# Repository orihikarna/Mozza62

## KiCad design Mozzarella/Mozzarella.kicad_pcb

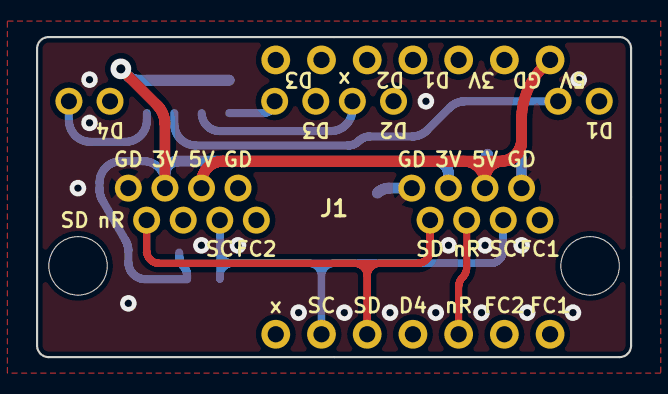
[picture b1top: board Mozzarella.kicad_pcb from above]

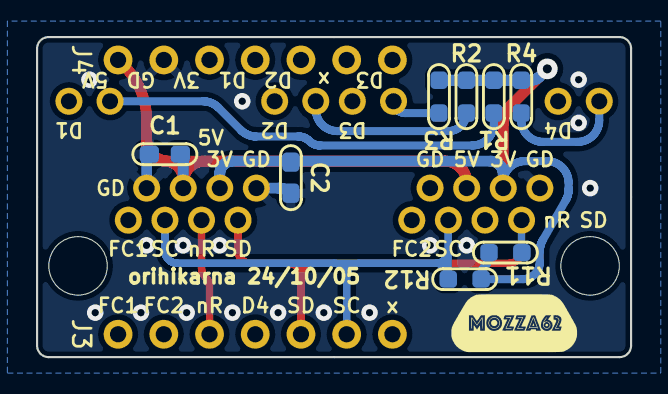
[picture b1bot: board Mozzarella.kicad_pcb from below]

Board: 4 copper layers, 33.0 x 17.8 mm, 12 parts (11 on the bottom side), 16 nets.

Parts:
C1, C2: 0.1u; C_1608_HandSolder
G1: LOGO; mozza62_logo2
J1: RJ45_LED_Shielded_x2; RJ45_Amphenol_RJHSE508X-02
J3, J4: Conn_01x07; PinHeader_1x07_P2.54mm_Vertical
R1, R2, R3, R4: 1k; R_1608_HandSolder
R11, R12: 2.2k; R_1608_HandSolder

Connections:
3V3: C2.1, J1.6, J1.18, J4.3, R1.1, R2.1, R3.1, R4.1, R11.2, R12.2
5VD: C1.1, J1.4, J1.16, J4.1
GND: C1.2, C2.2, J1.2, J1.8, J1.14, J1.20, J4.2
LED1: J1.9, J4.4
LED2: J1.11, J4.5
LED3: J1.21, J4.7
LED4: J1.23, J3.4
NRST: J1.5, J1.17, J3.3
unnamed: J1.10, R1.2
unnamed: J1.12, R2.2
unnamed: J1.22, R3.2
unnamed: J1.24, R4.2
RGB1: J1.1, J3.1
RGB2: J1.13, J3.2
SCK: J1.3, J1.15, J3.6, R12.1
SDA: J1.7, J1.19, J3.5, R11.1

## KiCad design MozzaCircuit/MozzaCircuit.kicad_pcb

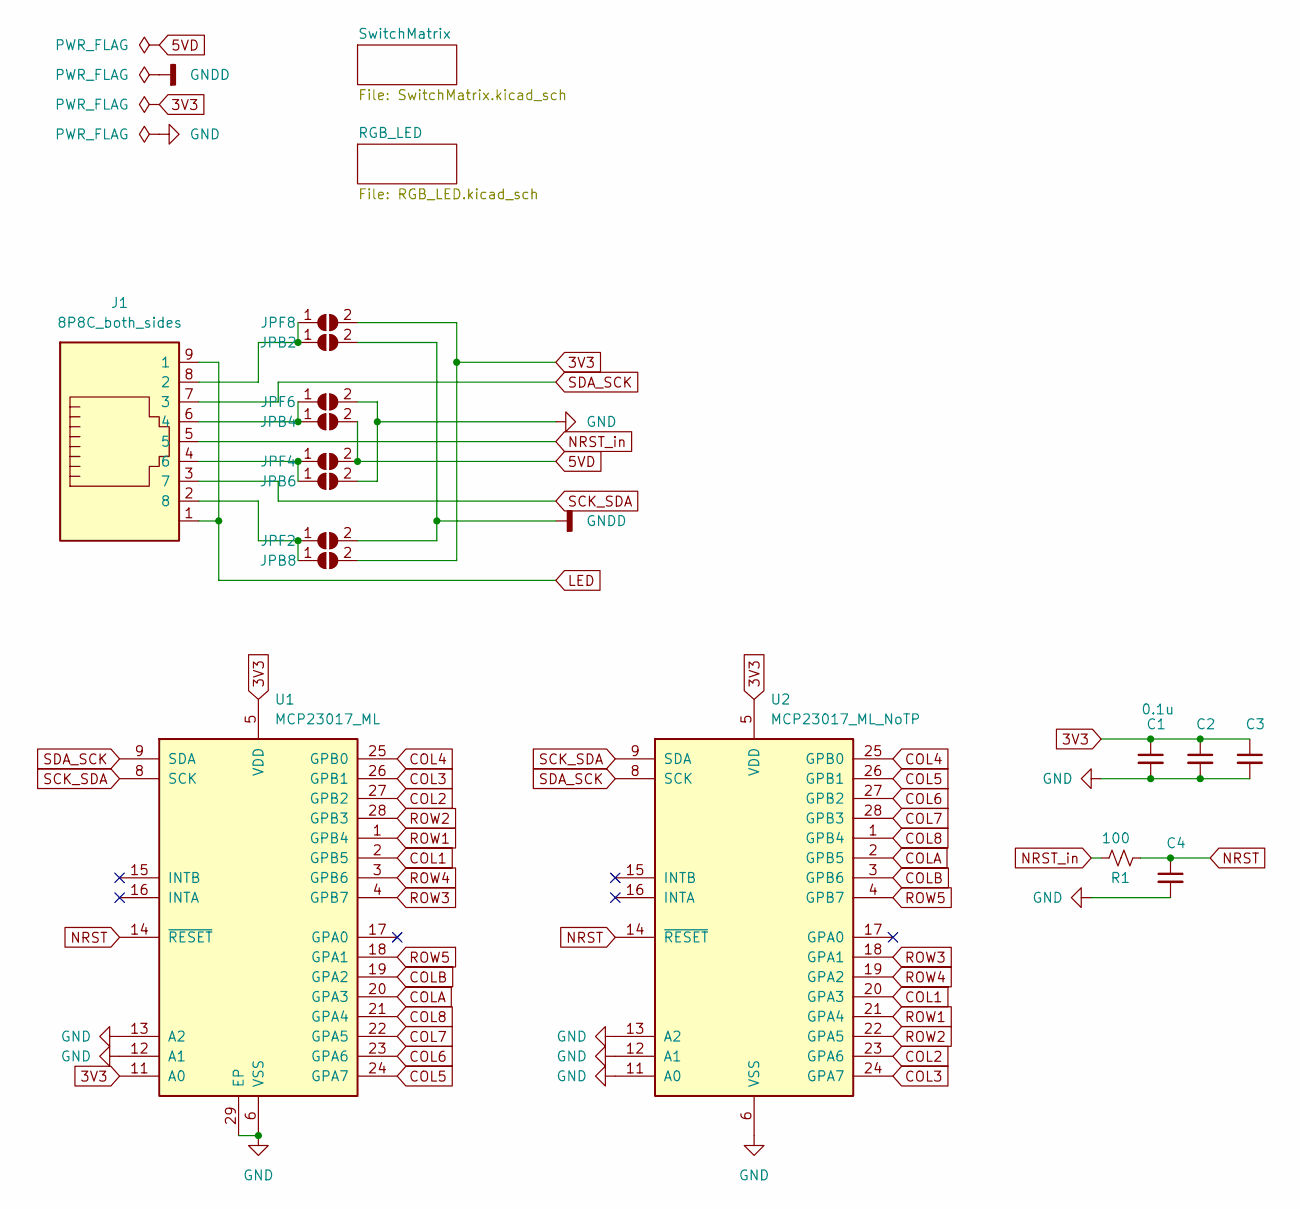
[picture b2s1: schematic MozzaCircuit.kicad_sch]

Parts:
C1: 0.1u; C_1608_HandSolder
C2: C_Small; C_1608_HandSolder
C3, C4: C_Small; C_1608_HandSolder_both_sides
J1: 8P8C_both_sides; RJ45_Molex_0955032884_both_sides
JPB2, JPB4, JPB6, JPB8: SolderJumper_2_Open; SolderJumper-2_P1.3mm_Open_TrianglePad1.0x1.5mm
JPF2, JPF4, JPF6, JPF8: SolderJumper_2_Open; SolderJumper-2_P1.3mm_Open_TrianglePad1.0x1.5mm
R1: 100; R_1608_HandSolder_both_sides
U1: MCP23017_ML; QFN-28-1EP_6x6mm_P0.65mm_EP4.25x4.25mm_Hand
U2: MCP23017_ML_NoTP; QFN-28-1EP_6x6mm_P0.65mm_EP4.25x4.25mm_Hand_NoTP

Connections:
3V3: C1.1, C2.1, C3.1, JPB8.2 (B), JPF8.2 (B), U1.5 (VDD), U1.11 (A0), U2.5 (VDD); also elsewhere on the board
5VD: JPB4.2 (B), JPF4.2 (B); also elsewhere on the board
COL1: U1.2 (GPB5), U2.20 (GPA3); also elsewhere on the board
COL2: U1.27 (GPB2), U2.23 (GPA6); also elsewhere on the board
COL3: U1.26 (GPB1), U2.24 (GPA7); also elsewhere on the board
COL4: U1.25 (GPB0), U2.25 (GPB0); also elsewhere on the board
COL5: U1.24 (GPA7), U2.26 (GPB1); also elsewhere on the board
COL6: U1.23 (GPA6), U2.27 (GPB2); also elsewhere on the board
COL7: U1.22 (GPA5), U2.28 (GPB3); also elsewhere on the board
COL8: U1.21 (GPA4), U2.1 (GPB4); also elsewhere on the board
COLA: U1.20 (GPA3), U2.2 (GPB5); also elsewhere on the board
COLB: U1.19 (GPA2), U2.3 (GPB6); also elsewhere on the board
GND: C1.2, C2.2, C3.2, C4.2, JPB6.2 (B), JPF6.2 (B), U1.6 (VSS), U1.12 (A1), U1.13 (A2), U1.29 (EP), U2.6 (VSS), U2.11 (A0), U2.12 (A1), U2.13 (A2); also elsewhere on the board
GNDD: JPB2.2 (B), JPF2.2 (B); also elsewhere on the board
LED: J1.1, J1.9 (1); also elsewhere on the board
NRST: C4.1, R1.2, U1.14 (~RESET), U2.14 (~RESET)
NRST_in: J1.5, R1.1
unnamed: J1.2 (8), JPB8.1 (A), JPF2.1 (A)
unnamed: J1.4 (6), JPB6.1 (A), JPF4.1 (A)
unnamed: J1.6 (4), JPB4.1 (A), JPF6.1 (A)
unnamed: J1.8 (2), JPB2.1 (A), JPF8.1 (A)
ROW1: U1.1 (GPB4), U2.21 (GPA4); also elsewhere on the board
ROW2: U1.28 (GPB3), U2.22 (GPA5); also elsewhere on the board
ROW3: U1.4 (GPB7), U2.18 (GPA1); also elsewhere on the board
ROW4: U1.3 (GPB6), U2.19 (GPA2); also elsewhere on the board
ROW5: U1.18 (GPA1), U2.4 (GPB7); also elsewhere on the board
SCK_SDA: J1.3 (7), U1.8 (SCK), U2.9 (SDA)
SDA_SCK: J1.7 (3), U1.9 (SDA), U2.8 (SCK)

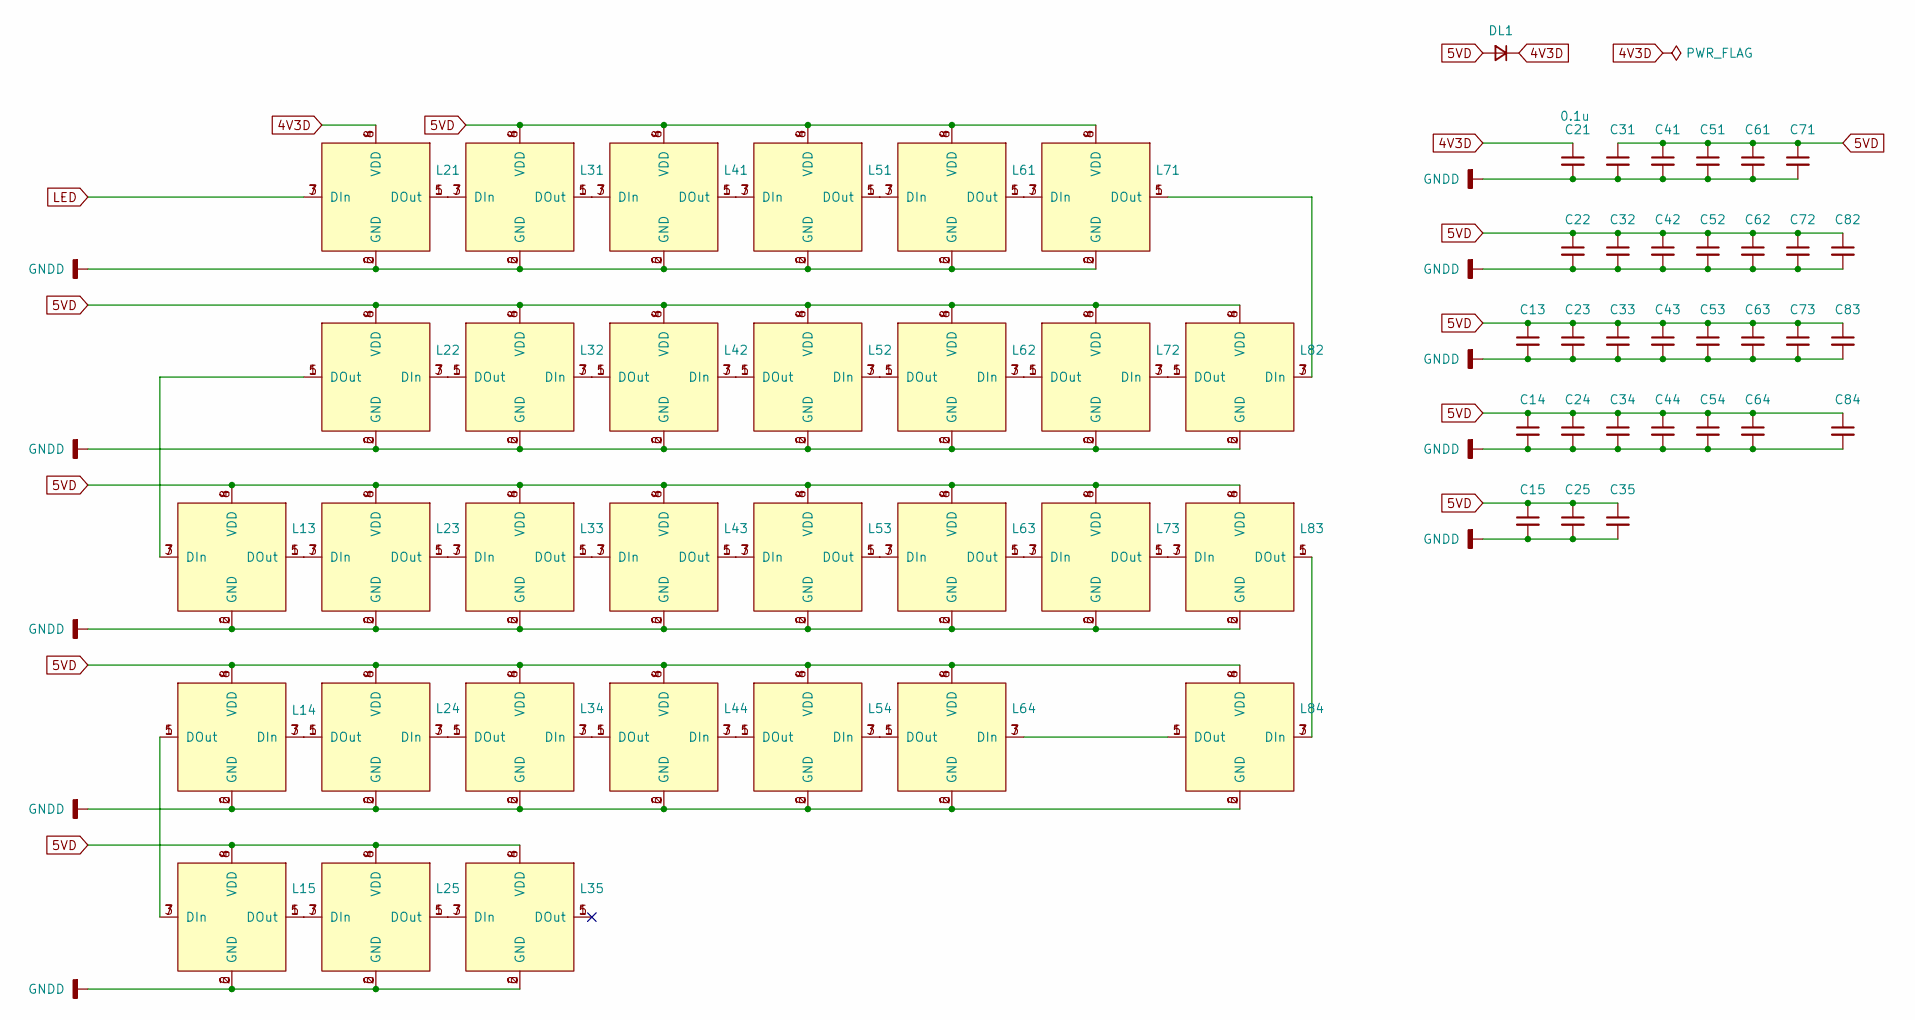
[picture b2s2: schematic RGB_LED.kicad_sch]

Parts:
C13, C14, C15, C22, C23, C24, C25, C31, C32, C33, C34, C35, C41, C42, C43, C44, C51, C52, C53, C54, C61, C62, C63, C64, C71, C72, C73, C82, C83, C84: C_Small; C_1608_HandSolder_both_sides
C21: 0.1u; C_1608_HandSolder_both_sides
DL1: D_Small; D_SOD-323_both_sides
L13, L14, L15, L21, L22, L23, L24, L25, L31, L32, L33, L34, L35, L41, L42, L43, L44, L51, L52, L53, L54, L61, L62, L63, L64, L71, L72, L73, L82, L83, L84: WS2812-2020_both_sides; WS2812B_2020_rev

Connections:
4V3D: C21.1, DL1.1 (K), L21.4 (VDD), L21.8; also elsewhere on the board
5VD: C13.1, C14.1, C15.1, C22.1, C23.1, C24.1, C25.1, C31.1, C32.1, C33.1, C34.1, C35.1, C41.1, C42.1, C43.1, C44.1, C51.1, C52.1, C53.1, C54.1, C61.1, C62.1, C63.1, C64.1, C71.1, C72.1, C73.1, C82.1, C83.1, C84.1, DL1.2 (A), L13.4 (VDD), L13.8, L14.4 (VDD), L14.8, L15.4 (VDD), L15.8, L22.4 (VDD), L22.8, L23.4 (VDD), L23.8, L24.4 (VDD), L24.8, L25.4 (VDD), L25.8, L31.4 (VDD), L31.8, L32.4 (VDD), L32.8, L33.4 (VDD), L33.8, L34.4 (VDD), L34.8, L35.4 (VDD), L35.8, L41.4 (VDD), L41.8, L42.4 (VDD), L42.8, L43.4 (VDD), L43.8, L44.4 (VDD), L44.8, L51.4 (VDD), L51.8, L52.4 (VDD), L52.8, L53.4 (VDD), L53.8, L54.4 (VDD), L54.8, L61.4 (VDD), L61.8, L62.4 (VDD), L62.8, L63.4 (VDD), L63.8, L64.4 (VDD), L64.8, L71.4 (VDD), L71.8, L72.4 (VDD), L72.8, L73.4 (VDD), L73.8, L82.4 (VDD), L82.8, L83.4 (VDD), L83.8, L84.4 (VDD), L84.8; also elsewhere on the board
GNDD: C13.2, C14.2, C15.2, C21.2, C22.2, C23.2, C24.2, C25.2, C31.2, C32.2, C33.2, C34.2, C35.2, C41.2, C42.2, C43.2, C44.2, C51.2, C52.2, C53.2, C54.2, C61.2, C62.2, C63.2, C64.2, C71.2, C72.2, C73.2, C82.2, C83.2, C84.2, L13.2 (GND), L13.6, L14.2 (GND), L14.6, L15.2 (GND), L15.6, L21.2 (GND), L21.6, L22.2 (GND), L22.6, L23.2 (GND), L23.6, L24.2 (GND), L24.6, L25.2 (GND), L25.6, L31.2 (GND), L31.6, L32.2 (GND), L32.6, L33.2 (GND), L33.6, L34.2 (GND), L34.6, L35.2 (GND), L35.6, L41.2 (GND), L41.6, L42.2 (GND), L42.6, L43.2 (GND), L43.6, L44.2 (GND), L44.6, L51.2 (GND), L51.6, L52.2 (GND), L52.6, L53.2 (GND), L53.6, L54.2 (GND), L54.6, L61.2 (GND), L61.6, L62.2 (GND), L62.6, L63.2 (GND), L63.6, L64.2 (GND), L64.6, L71.2 (GND), L71.6, L72.2 (GND), L72.6, L73.2 (GND), L73.6, L82.2 (GND), L82.6, L83.2 (GND), L83.6, L84.2 (GND), L84.6; also elsewhere on the board
LED: L21.3 (DIn), L21.7 (DIn); also elsewhere on the board
unnamed: L13.1 (DOut), L13.5 (DOut), L23.3 (DIn), L23.7 (DIn)
unnamed: L13.3 (DIn), L13.7 (DIn), L22.1 (DOut), L22.5 (DOut)
unnamed: L14.1 (DOut), L14.5 (DOut), L15.3 (DIn), L15.7 (DIn)
unnamed: L14.3 (DIn), L14.7 (DIn), L24.1 (DOut), L24.5 (DOut)
unnamed: L15.1 (DOut), L15.5 (DOut), L25.3 (DIn), L25.7 (DIn)
unnamed: L21.1 (DOut), L21.5 (DOut), L31.3 (DIn), L31.7 (DIn)
unnamed: L22.3 (DIn), L22.7 (DIn), L32.1 (DOut), L32.5 (DOut)
unnamed: L23.1 (DOut), L23.5 (DOut), L33.3 (DIn), L33.7 (DIn)
unnamed: L24.3 (DIn), L24.7 (DIn), L34.1 (DOut), L34.5 (DOut)
unnamed: L25.1 (DOut), L25.5 (DOut), L35.3 (DIn), L35.7 (DIn)
unnamed: L31.1 (DOut), L31.5 (DOut), L41.3 (DIn), L41.7 (DIn)
unnamed: L32.3 (DIn), L32.7 (DIn), L42.1 (DOut), L42.5 (DOut)
unnamed: L33.1 (DOut), L33.5 (DOut), L43.3 (DIn), L43.7 (DIn)
unnamed: L34.3 (DIn), L34.7 (DIn), L44.1 (DOut), L44.5 (DOut)
unnamed: L41.1 (DOut), L41.5 (DOut), L51.3 (DIn), L51.7 (DIn)
unnamed: L42.3 (DIn), L42.7 (DIn), L52.1 (DOut), L52.5 (DOut)
unnamed: L43.1 (DOut), L43.5 (DOut), L53.3 (DIn), L53.7 (DIn)
unnamed: L44.3 (DIn), L44.7 (DIn), L54.1 (DOut), L54.5 (DOut)
unnamed: L51.1 (DOut), L51.5 (DOut), L61.3 (DIn), L61.7 (DIn)
unnamed: L52.3 (DIn), L52.7 (DIn), L62.1 (DOut), L62.5 (DOut)
unnamed: L53.1 (DOut), L53.5 (DOut), L63.3 (DIn), L63.7 (DIn)
unnamed: L54.3 (DIn), L54.7 (DIn), L64.1 (DOut), L64.5 (DOut)
unnamed: L61.1 (DOut), L61.5 (DOut), L71.3 (DIn), L71.7 (DIn)
unnamed: L62.3 (DIn), L62.7 (DIn), L72.1 (DOut), L72.5 (DOut)
unnamed: L63.1 (DOut), L63.5 (DOut), L73.3 (DIn), L73.7 (DIn)
unnamed: L64.3 (DIn), L64.7 (DIn), L84.1 (DOut), L84.5 (DOut)
unnamed: L71.1 (DOut), L71.5 (DOut), L82.3 (DIn), L82.7 (DIn)
unnamed: L72.3 (DIn), L72.7 (DIn), L82.1 (DOut), L82.5 (DOut)
unnamed: L73.1 (DOut), L73.5 (DOut), L83.3 (DIn), L83.7 (DIn)
unnamed: L83.1 (DOut), L83.5 (DOut), L84.3 (DIn), L84.7 (DIn)

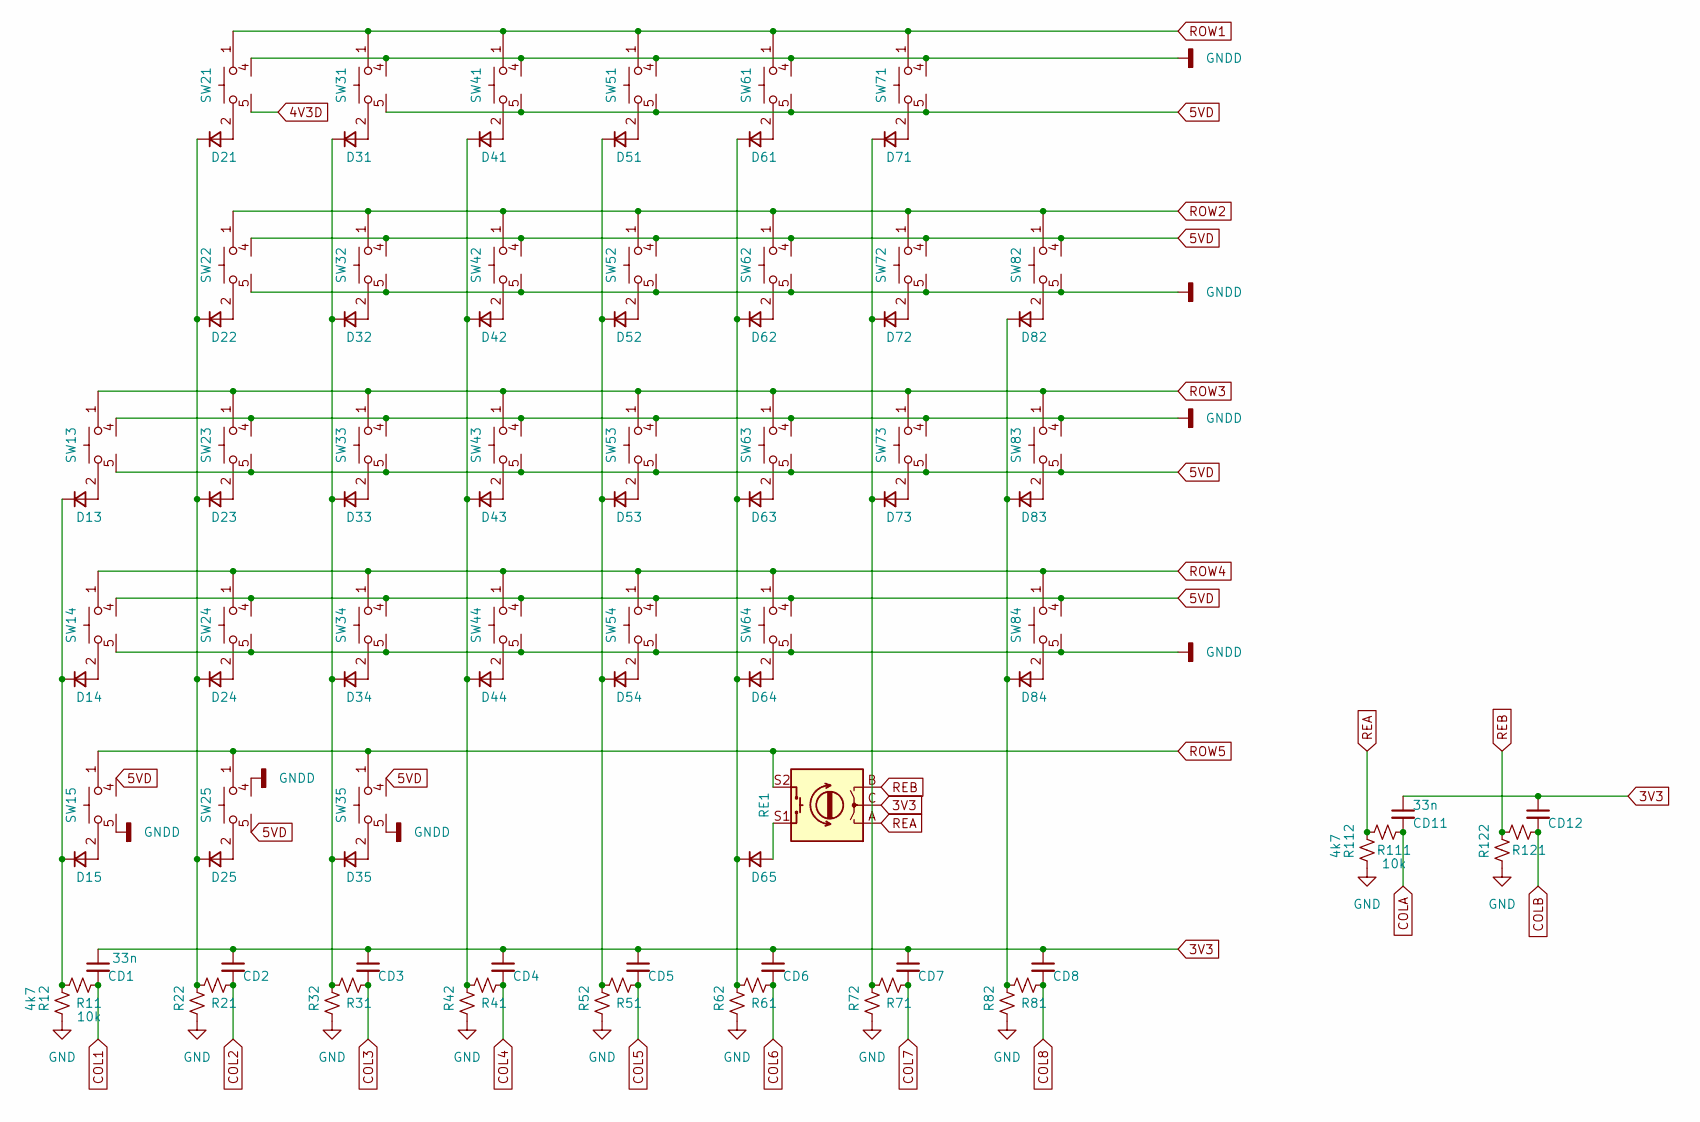
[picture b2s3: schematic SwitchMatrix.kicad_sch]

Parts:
CD1, CD11: 33n; C_1608_HandSolder_both_sides
CD2, CD3, CD4, CD5, CD6, CD7, CD8, CD12: C_Small; C_1608_HandSolder_both_sides
D13, D14, D15, D21, D22, D23, D24, D25, D31, D32, D33, D34, D35, D41, D42, D43, D44, D51, D52, D53, D54, D61, D62, D63, D64, D65, D71, D72, D73, D82, D83, D84: D_Small; D_SOD-323_both_sides
R11, R111: 10k; R_1608_HandSolder_both_sides
R12, R112: 4k7; R_1608_HandSolder_both_sides
R21, R22, R31, R32, R41, R42, R51, R52, R61, R62, R71, R72, R81, R82, R121, R122: R_Small_US; R_1608_HandSolder_both_sides
RE1: RotaryEncoder_Switch; RotaryEncoder_Bourns_PEC12R-4215F
SW13, SW14, SW15, SW21, SW22, SW23, SW24, SW25, SW31, SW32, SW33, SW34, SW35, SW41, SW42, SW43, SW44, SW51, SW52, SW53, SW54, SW61, SW62, SW63, SW64, SW71, SW72, SW73, SW82, SW83, SW84: SW_ChocV2_rev; ChocV2_rev

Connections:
3V3: CD1.1, CD2.1, CD3.1, CD4.1, CD5.1, CD6.1, CD7.1, CD8.1, CD11.1, CD12.1, RE1.C; also elsewhere on the board
4V3D: SW21.5; also elsewhere on the board
5VD: SW13.5, SW14.4, SW15.4, SW22.4, SW23.5, SW24.4, SW25.5, SW31.5, SW32.4, SW33.5, SW34.4, SW35.4, SW41.5, SW42.4, SW43.5, SW44.4, SW51.5, SW52.4, SW53.5, SW54.4, SW61.5, SW62.4, SW63.5, SW64.4, SW71.5, SW72.4, SW73.5, SW82.4, SW83.5, SW84.4; also elsewhere on the board
COL1: CD1.2, R11.2; also elsewhere on the board
COL2: CD2.2, R21.2; also elsewhere on the board
COL3: CD3.2, R31.2; also elsewhere on the board
COL4: CD4.2, R41.2; also elsewhere on the board
COL5: CD5.2, R51.2; also elsewhere on the board
COL6: CD6.2, R61.2; also elsewhere on the board
COL7: CD7.2, R71.2; also elsewhere on the board
COL8: CD8.2, R81.2; also elsewhere on the board
COLA: CD11.2, R111.2; also elsewhere on the board
COLB: CD12.2, R121.2; also elsewhere on the board
GND: R12.2, R22.2, R32.2, R42.2, R52.2, R62.2, R72.2, R82.2, R112.2, R122.2; also elsewhere on the board
GNDD: SW13.4, SW14.5, SW15.5, SW21.4, SW22.5, SW23.4, SW24.5, SW25.4, SW31.4, SW32.5, SW33.4, SW34.5, SW35.5, SW41.4, SW42.5, SW43.4, SW44.5, SW51.4, SW52.5, SW53.4, SW54.5, SW61.4, SW62.5, SW63.4, SW64.5, SW71.4, SW72.5, SW73.4, SW82.5, SW83.4, SW84.5; also elsewhere on the board
unnamed: D13.1 (K), D14.1 (K), D15.1 (K), R11.1, R12.1
unnamed: D13.2 (A), SW13.2, SW13.3
unnamed: D14.2 (A), SW14.2, SW14.3
unnamed: D15.2 (A), SW15.2, SW15.3
unnamed: D21.1 (K), D22.1 (K), D23.1 (K), D24.1 (K), D25.1 (K), R21.1, R22.1
unnamed: D21.2 (A), SW21.2, SW21.3
unnamed: D22.2 (A), SW22.2, SW22.3
unnamed: D23.2 (A), SW23.2, SW23.3
unnamed: D24.2 (A), SW24.2, SW24.3
unnamed: D25.2 (A), SW25.2, SW25.3
unnamed: D31.1 (K), D32.1 (K), D33.1 (K), D34.1 (K), D35.1 (K), R31.1, R32.1
unnamed: D31.2 (A), SW31.2, SW31.3
unnamed: D32.2 (A), SW32.2, SW32.3
unnamed: D33.2 (A), SW33.2, SW33.3
unnamed: D34.2 (A), SW34.2, SW34.3
unnamed: D35.2 (A), SW35.2, SW35.3
unnamed: D41.1 (K), D42.1 (K), D43.1 (K), D44.1 (K), R41.1, R42.1
unnamed: D41.2 (A), SW41.2, SW41.3
unnamed: D42.2 (A), SW42.2, SW42.3
unnamed: D43.2 (A), SW43.2, SW43.3
unnamed: D44.2 (A), SW44.2, SW44.3
unnamed: D51.1 (K), D52.1 (K), D53.1 (K), D54.1 (K), R51.1, R52.1
unnamed: D51.2 (A), SW51.2, SW51.3
unnamed: D52.2 (A), SW52.2, SW52.3
unnamed: D53.2 (A), SW53.2, SW53.3
unnamed: D54.2 (A), SW54.2, SW54.3
unnamed: D61.1 (K), D62.1 (K), D63.1 (K), D64.1 (K), D65.1 (K), R61.1, R62.1
unnamed: D61.2 (A), SW61.2, SW61.3
unnamed: D62.2 (A), SW62.2, SW62.3
unnamed: D63.2 (A), SW63.2, SW63.3
unnamed: D64.2 (A), SW64.2, SW64.3
unnamed: D65.2 (A), RE1.S1
unnamed: D71.1 (K), D72.1 (K), D73.1 (K), R71.1, R72.1
unnamed: D71.2 (A), SW71.2, SW71.3
unnamed: D72.2 (A), SW72.2, SW72.3
unnamed: D73.2 (A), SW73.2, SW73.3
unnamed: D82.1 (K), D83.1 (K), D84.1 (K), R81.1, R82.1
unnamed: D82.2 (A), SW82.2, SW82.3
unnamed: D83.2 (A), SW83.2, SW83.3
unnamed: D84.2 (A), SW84.2, SW84.3
REA: R111.1, R112.1, RE1.A
REB: R121.1, R122.1, RE1.B
ROW1: SW21.1, SW31.1, SW41.1, SW51.1, SW61.1, SW71.1; also elsewhere on the board
ROW2: SW22.1, SW32.1, SW42.1, SW52.1, SW62.1, SW72.1, SW82.1; also elsewhere on the board
ROW3: SW13.1, SW23.1, SW33.1, SW43.1, SW53.1, SW63.1, SW73.1, SW83.1; also elsewhere on the board
ROW4: SW14.1, SW24.1, SW34.1, SW44.1, SW54.1, SW64.1, SW84.1; also elsewhere on the board
ROW5: RE1.S2, SW15.1, SW25.1, SW35.1; also elsewhere on the board

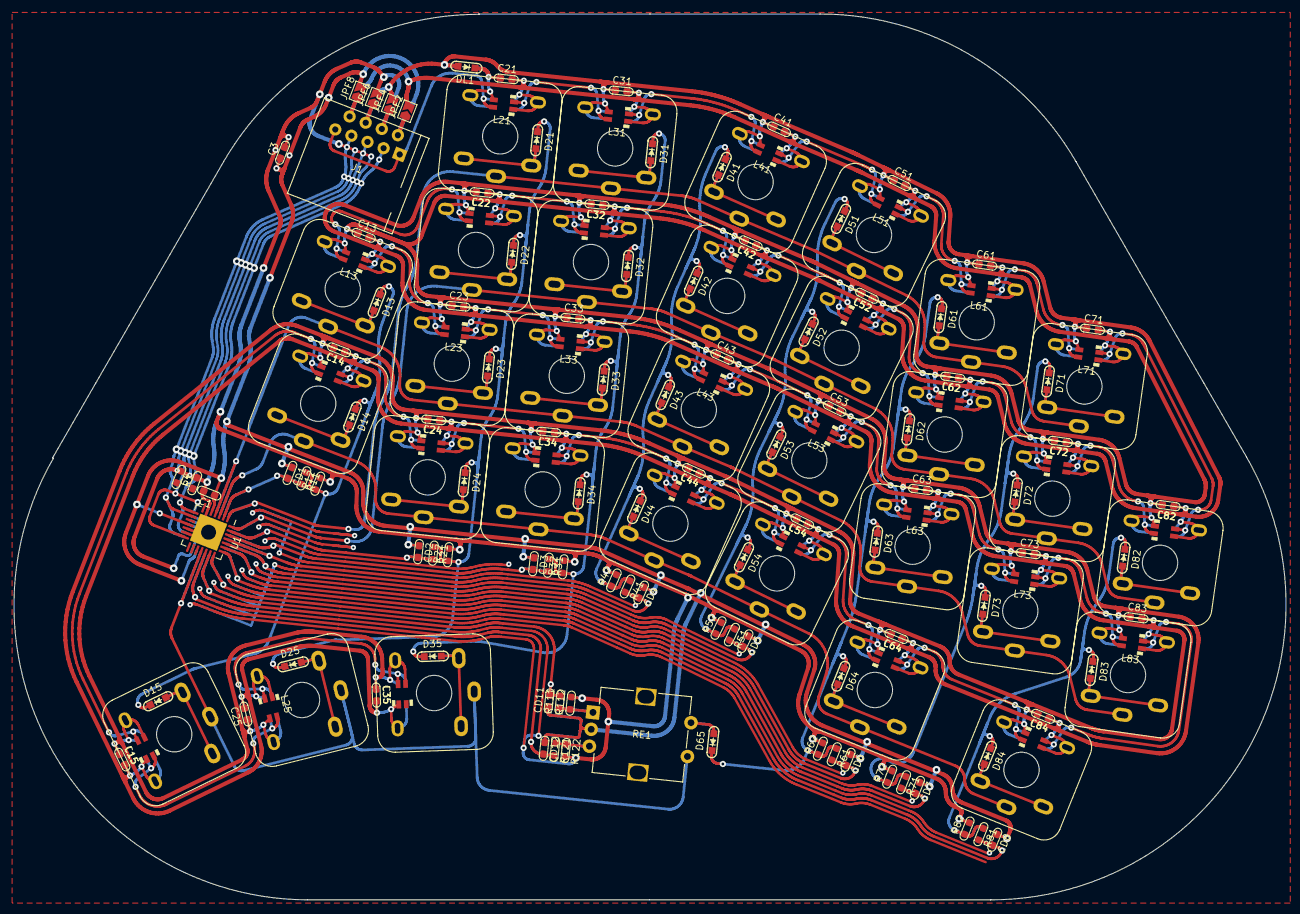
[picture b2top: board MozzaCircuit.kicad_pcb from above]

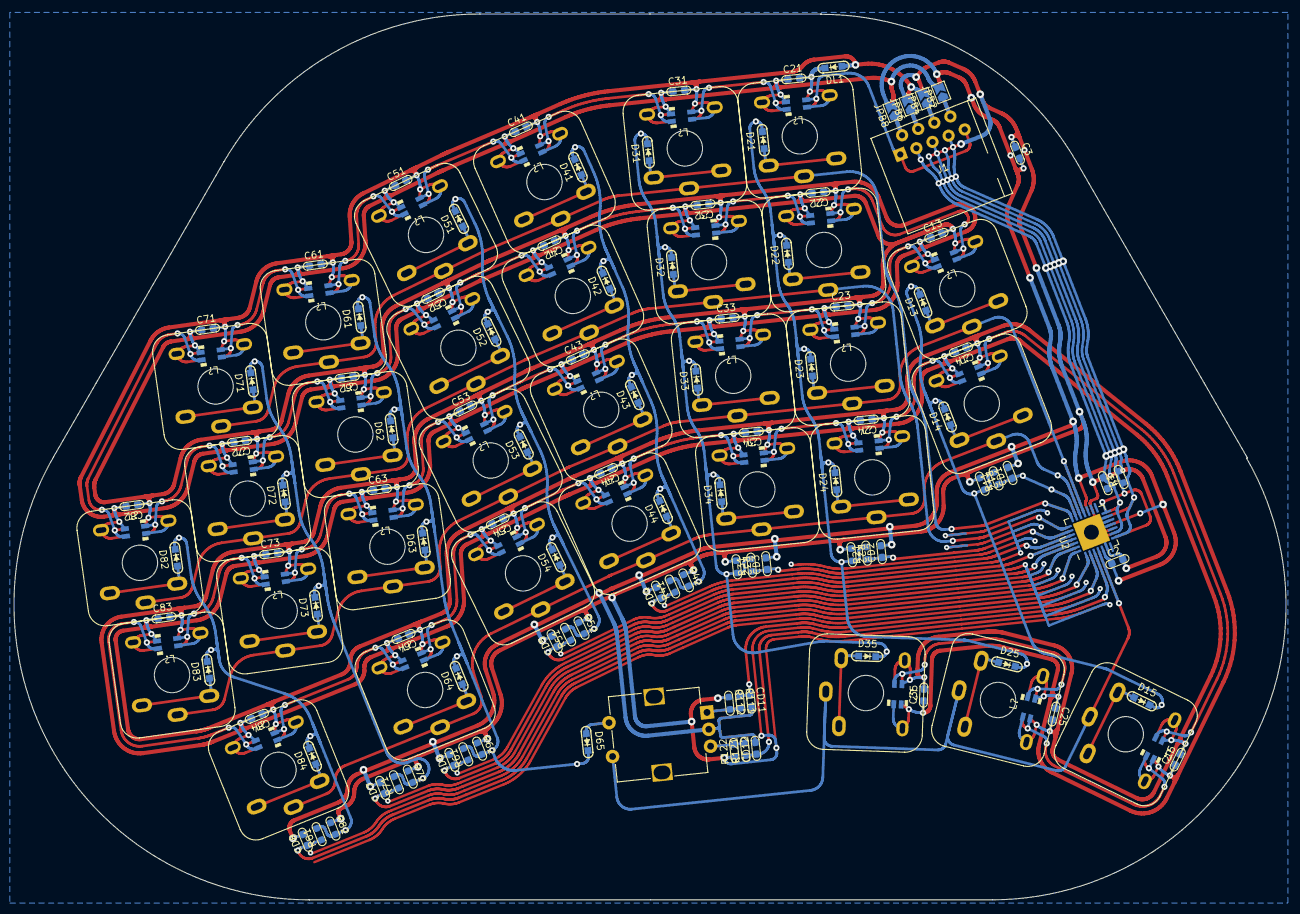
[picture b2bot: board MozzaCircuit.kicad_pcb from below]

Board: 2 copper layers, 187.1 x 130.3 mm, 173 parts (7 on the bottom side), 101 nets.

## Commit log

2022-08-19 added pythonand scad scripts for encode knob
2022-08-19 adjust size, avoid elephant foot
2022-08-20 4-th degree curve, axis bottom radius = 7mm, revert bump size
2022-08-20 added 2 keys
2022-08-20 added rules for new keys
2022-08-20 reduce wall thickness, star walls
2022-08-24 2nd print
2022-08-25 3rd print
2022-08-26 4th print
2022-08-26 simplifying
2022-08-27 5th print
2022-08-27 tested egg shapes
2022-08-28 changed pinky bottom angle
2022-08-28 6th print
2022-08-30 7th print
2022-11-26 no10 (edgecuts)
2022-11-27 no11
2022-12-11 hexagonal edge cuts
2022-12-12 round shape
2022-12-17 more round corner (15deg)
2022-12-17 add keyparts symbol lib
2022-12-21 added footprints
2022-12-25 sw schema
2022-12-25 switch matrix
2022-12-25 added rotary encoder
2022-12-28 led matrix
2022-12-28 added rj45
2022-12-28 removed unused sch
2022-12-28 added 3D models, debounce for encoder
2022-12-29 added qfn footprints
2022-12-29 init pcb
2022-12-31 choc separate pins, qfn no tp, led oval hole
2022-12-31 kicad output
2022-12-31 started place and route
2022-12-31 placed sw and led
2022-12-31 led direction
2023-01-01 1608 R&C
2023-01-01 led power
2023-01-03 led wiring
2023-01-03 refactoring bezier corner
2023-01-04 arc corner wiring
2023-01-04 led dat wiring
2023-01-05 led wiring, fix fp silk overlaps
2023-01-05 clearance settings
2023-01-05 fixed diode fp courtyard
2023-01-06 footprint circles, fix switch sch
2023-01-07 cleaned zigzag code
2023-01-07 mod, pad accessor
2023-01-07 led pwr wiring
2023-01-12 horizontal wiring
2023-01-12 led horz wiring
2023-01-12 led diode wiring
2023-01-12 fix R footprint
2023-01-13 placed all fp roughly
2023-01-13 fp refs
2023-01-14 connecting diode cols
2023-01-15 column diodes
2023-01-15 3V3 row line
2023-01-19 wiring debounce
2023-01-19 wiring debouse
2023-01-26 debounce row wiring
2023-01-27 debounce gnd
2023-01-27 led right ends wiring
2023-01-28 thumb led wiring
2023-01-28 led left end
2023-01-29 rotend debounce
2023-01-30 placing led vias for wiring
2023-01-31 led wire vias
2023-01-31 clean up
2023-02-01 thumb diodes
2023-02-02 adding horz para lines
2023-02-03 rotate rot_enc
2023-02-05 rotenc dbnc via, exp vias
2023-02-06 expander vias
2023-02-08 drawing exp horz lines
2023-02-09 exp wires
2023-02-10 redid debounce
2023-02-11 exp horz lines
2023-02-11 exp wire param adjust
2023-02-12 led pwr line, row vert lines
2023-02-14 wiring rj45
2023-02-19 rj45 wiring
2023-02-22 rj45 circular wiring
2023-02-25 autopep8
2023-02-25 kadpy module
2023-02-25 format
2023-02-25 dird format
2023-03-05 rj45 - exp wiring
2023-03-08 row & dbnc pwr
2023-03-11 led power, rotenc power
2023-03-11 formatted
2023-03-18 no drc errors finally
2023-03-18 modified i2c addr
2023-03-18 edge.cuts by corners
2023-03-18 removed edge.cuts points
2023-03-18 added zones
2023-03-19 removed unneeded led vias
2023-03-19 led vias
2023-03-19 cleaning row led lines
2023-03-19 minor mods
2023-03-20 debounce rows
2023-03-21 finished rotenc
2023-03-21 increased power via size
2023-03-21 rj45 --> led
2023-03-22 led right ends
2023-03-25 led thumbing
2023-03-25 led reduced a via, thumbs
2023-03-25 led thumbs done
2023-03-26 led thumb lines
2023-03-26 via size, line width adjustment
2023-03-26 dbnc position & wiring adjustment
2023-03-26 rotenc diode
2023-03-26 col8 dbnc vcc
2023-03-26 rj45 jumpers
2023-04-08 rj45 to exp wire
2023-04-08 rename exp via
2023-04-09 col lines
2023-04-12 col horz lines
2023-04-16 led lines
2023-04-16 localize led vias
2023-04-19 led line ctr
2023-04-19 led func
2023-04-22 col horz gnd vias
2023-04-23 row1/2 vias
2023-04-29 exp wire
2023-04-29 exp gnd vias
2023-04-29 cleaned
2023-05-02 exp flower
2023-05-03 exp gnd lines
2023-05-04 fix DRC errors
2023-05-05 adjust board size and rj45 pos
2023-05-05 adjusted board size and rj45 pos
2023-05-05 exp vias & wires
2023-05-06 added power cap
2023-05-07 drc passed
2023-05-07 added gnd via to avoid warning
2023-05-07 gnd vias
2023-05-07 key gnd vias
2023-05-08 swap gnd and 3v3 of rj45
2023-05-08 silk screen
2023-05-11 guarding row1,2
2023-05-11 added gnd via for col1
2023-05-11 added gnd via for rj45
2023-05-11 adjusted gnd vias
2023-05-11 fixed gnd trace
2023-05-13 added sw gnd vias
2023-05-14 changed row lines to have better ground fill
2023-05-14 fixed drc errors
2023-05-15 added gnd vias
2023-05-16 minor adjustments
2023-05-16 col horz lines & led 4-thumb adjust
2023-05-20 adjust gnd vias
2023-05-20 cleand
2023-05-21 edgecuts, gnd vias, screw holes
2023-05-27 enlarged holes of rj45 & rotenc
2023-05-28 edge cuts
2023-06-01 added logo, part holes
2023-06-03 edge.cuts, logo
2023-06-03 added Bottom plate, mod_props.json
2023-06-03 bottom svg
2023-06-10 trying rule areas
2023-06-11 onigiri patterns
2023-06-11 back side
2023-06-11 cleaned a bit
2023-06-11 board names
2023-06-11 added middle, spacer, top boards
2023-06-11 added logo
2023-06-11 added board name
2023-06-12 spacer holes
2023-06-17 add rule areas
2023-06-17 rj45 adjust
2023-06-17 big hole for spacer plate
2023-06-18 cap/resister values
2023-06-18 top plate
2023-06-18 adjusted
2023-06-18 fixed rj45 foot print
2023-06-18 export dxf
2023-06-18 plot SVG, convert it to DXF
2023-06-18 top plate pdf
2023-06-18 generated gerber files
2023-06-24 added mozzarella board
2023-06-27 cleaned rj45 foot print
2023-07-01 key layout
2023-07-04 scad output
2023-07-24 initial led & mcp check
2023-07-29 M5Atom-Matrix full led, switch
2023-08-11 add platformio project
2023-08-12 add i2c
2023-08-13 i2c keyscan check
2023-08-19 started right side
2023-08-19 changed to m5atom board
2023-08-26 right side
2023-10-28 working on key scanner
2023-10-29 update key sw layout, not working
2023-10-29 fixed key scan
2023-11-03 impl rot switches
2023-11-04 renamed
2023-11-04 added buffers
2024-08-24 add layer
2024-08-24 avoid clang format
2024-08-29 add json
2024-08-29 adding led feature
2024-08-29 set color by adafruit
2024-08-30 fix led number
2024-08-30 measure led time
2024-08-30 rename, ConfigData
2024-08-30 call init()
2024-08-30 update keymaps
2024-08-30 windmill effect
2024-08-30 overlay led
2024-08-31 adjust led effects
2024-08-31 white overlay
2024-08-31 wip unmod & nkro
2024-08-31 clean nkro
2024-08-31 fixed tick type
2024-09-03 replaced BLE library to fix conection problem
2024-09-06 lower log level, fix led period
2024-09-07 add emacs translation
2024-09-07 add keybstatus for led
2024-09-09 if unpluged, zero clear col
2024-09-14 cable disconnect
2024-09-14 adjusted status led color
2024-09-15 moving to nRF xiao
2024-09-15 build passed?
2024-09-16 fixed name
2024-09-16 don't wait serial
2024-09-16 ble name, board led (wip)
2024-09-18 fix compile error
2024-09-18 rewiring
2024-09-19 start wiring rella
2024-09-20 placed
2024-09-20 wiring
2024-09-22 led on green
2024-09-22 hide xial mod
2024-09-23 changing led r side
2024-09-23 fixed r wires
2024-09-23 fixed board height
2024-09-24 refs
2024-09-26 add caps
2024-09-28 i2c regs wip
2024-09-28 rgb1 wire
2024-09-29 adjusted reg row lines
2024-10-01 wired
2024-10-02 add zones
2024-10-03 adjusted zone
2024-10-04 add logo
2024-10-05 final check
2024-10-05 generated gerber
2024-10-29 add esp32 env
2024-10-31 add esp32 proj
2024-11-01 fix board name
2024-11-01 fixed led
2024-11-02 fix led blinks
2024-12-30 update [Tab] key position, update for Python updates
2025-09-05 update library
2025-09-05 fixed type
2025-09-06 fixed library version
2025-09-21 test ble paring
2025-09-21 win map
2025-09-21 add new config
2025-09-21 add formatter setting
2025-09-21 use nimble 1.4.x
2025-09-21 new config didn't work on S3
2025-09-23 add usb keyboard feature
2025-09-23 add iifdef
2025-09-23 mod keymap
2025-09-23 toggle emacs mode
2025-09-24 disavle LED
2025-09-26 insert unmod before emacs
2025-09-27 add ESP32C6 conf
2025-09-28 nrf52 support
2025-09-28 nrf52 passkey
2025-09-28 debug nimble log
2025-09-29 renamed header extension
